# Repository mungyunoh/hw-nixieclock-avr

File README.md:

hw-nixieclock-avr
=============

This project is deprecated and replaced by the arm version.

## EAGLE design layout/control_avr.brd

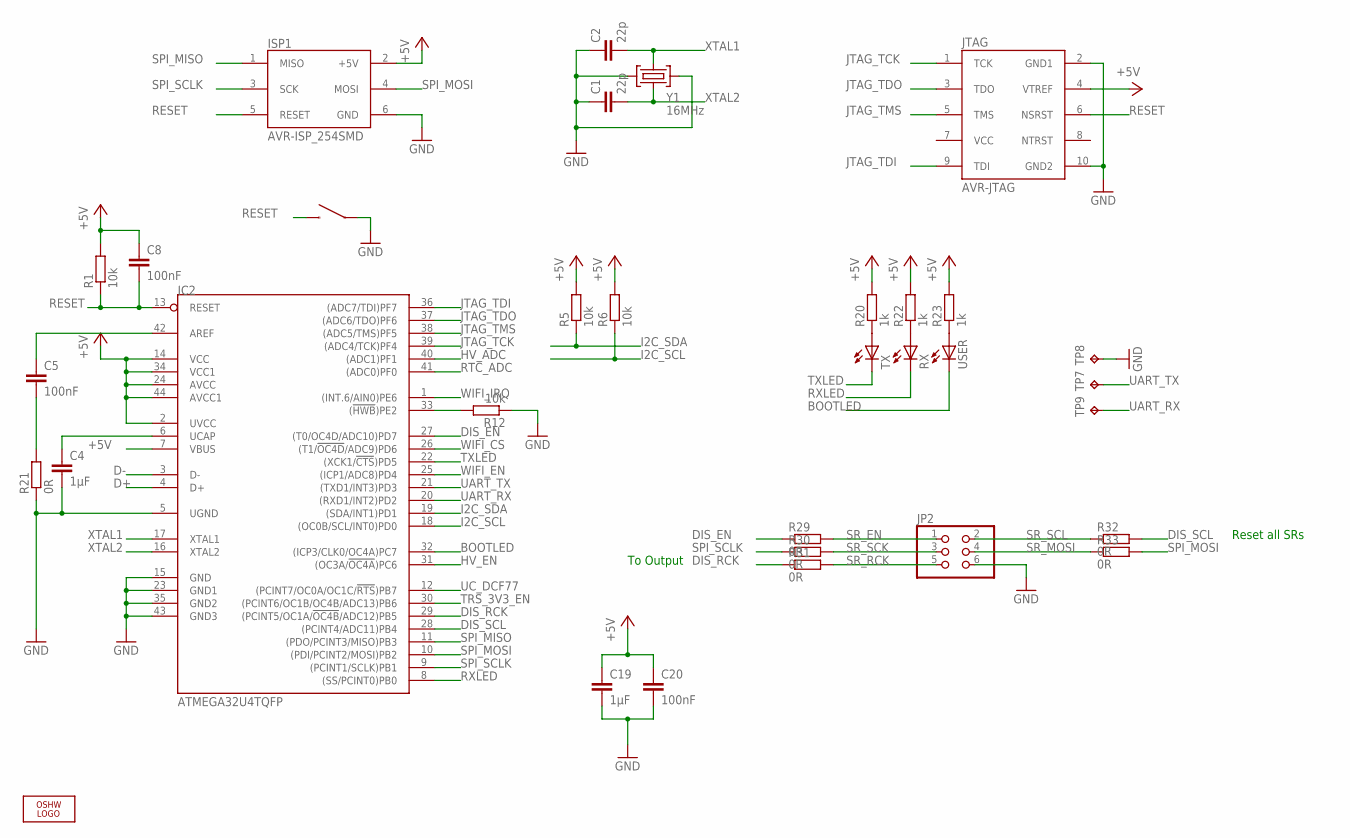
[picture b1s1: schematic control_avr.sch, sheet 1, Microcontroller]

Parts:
C1, C2: 22p; C0603
C4, C19: 1µF; C0603
C5, C8, C20: 100nF; C0603
IC2: ATMEGA32U4TQFP; TQFP44
ISP1: AVR-ISP_254SMD; 2X03SMD
JP2: PINHD-2X3_2.54-SMD-R; 2X03SMD/R
JTAG: AVR-JTAG; 20021121-10010XXLF
LOGO1: OSHW_LOGO_FILLX0200-NT; OSHW_FILLX200_NOTEXT
R1, R5, R6, R12: 10k; R0603
R20, R22, R23: 1k; R0603
R21, R29, R30, R31, R32, R33: 0R; R0603
RESET: TACT-SWITCH-47-35; 47-35
RX: LEDCHIP-LED0603; CHIP-LED0603
TP7, TP9: TPTP10R; TP10R
TP8: TPTP10SQ; TP10SQ
TX: LEDCHIP-LED0603; CHIP-LED0603
USER: LEDCHIP-LED0603; CHIP-LED0603
Y1: 16MHz; X22

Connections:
+5V: C8.1, C19.1, C20.1, IC2.2 (UVCC), IC2.7 (VBUS), IC2.14 (VCC), IC2.24 (AVCC), IC2.34 (VCC1), IC2.44 (AVCC1), ISP1.2 (+5V), JTAG.4 (VTREF), R1.2, R5.2, R6.2, R20.2, R22.2, R23.2; also elsewhere on the board
BOOTLED: IC2.32 ((ICP3/CLK0/OC4A)PC7), USER.C
D+: IC2.4 (D+); also elsewhere on the board
D-: IC2.3 (D-); also elsewhere on the board
DIS_EN: IC2.27 ((T0/OC4D/ADC10)PD7), R29.1
DIS_RCK: IC2.29 ((PCINT5/OC1A/!OC4B!/ADC12)PB5), R31.1
DIS_SCL: IC2.28 ((PCINT4/ADC11)PB4), R32.2
GND: C1.1, C2.1, C4.2, C19.2, C20.2, IC2.5 (UGND), IC2.15 (GND), IC2.23 (GND1), IC2.35 (GND2), IC2.43 (GND3), ISP1.6 (GND), JP2.6, JTAG.2 (GND1), JTAG.10 (GND2), R12.1, R21.1, RESET.C, RESET.D, TP8.TP, Y1.P$1 (GND1), Y1.P$3 (GND2); also elsewhere on the board
HV_ADC: IC2.40 ((ADC1)PF1); also elsewhere on the board
HV_EN: IC2.31 ((OC3A/!OC4A!)PC6); also elsewhere on the board
I2C_SCL: IC2.18 ((OC0B/SCL/INT0)PD0), R6.1; also elsewhere on the board
I2C_SDA: IC2.19 ((SDA/INT1)PD1), R5.1; also elsewhere on the board
JTAG_TCK: IC2.39 ((ADC4/TCK)PF4), JTAG.1 (TCK)
JTAG_TDI: IC2.36 ((ADC7/TDI)PF7), JTAG.9 (TDI)
JTAG_TDO: IC2.37 ((ADC6/TDO)PF6), JTAG.3 (TDO)
JTAG_TMS: IC2.38 ((ADC5/TMS)PF5), JTAG.5 (TMS)
unnamed: R20.1, TX.A
unnamed: IC2.33 ((!HWB!)PE2), R12.2
unnamed: C5.2, R21.2
unnamed: C5.1, IC2.42 (AREF)
unnamed: R22.1, RX.A
unnamed: R23.1, USER.A
RESET: C8.2, IC2.13 (RESET), ISP1.5 (RESET), JTAG.6 (NSRST), R1.1, RESET.A, RESET.B
RTC_ADC: IC2.41 ((ADC0)PF0); also elsewhere on the board
RXLED: IC2.8 ((SS/PCINT0)PB0), RX.C
SPI_MISO: IC2.11 ((PDO/PCINT3/MISO)PB3), ISP1.1 (MISO); also elsewhere on the board
SPI_MOSI: IC2.10 ((PDI/PCINT2/MOSI)PB2), ISP1.4 (MOSI), R33.2; also elsewhere on the board
SPI_SCLK: IC2.9 ((PCINT1/SCLK)PB1), ISP1.3 (SCK), R30.1; also elsewhere on the board
SR_EN: JP2.1, R29.2
SR_MOSI: JP2.4, R33.1
SR_RCK: JP2.5, R31.2
SR_SCK: JP2.3, R30.2
SR_SCL: JP2.2, R32.1
TRS_3V3_EN: IC2.30 ((PCINT6/OC1B/OC4B/ADC13)PB6); also elsewhere on the board
TXLED: IC2.22 ((XCK1/!CTS!)PD5), TX.C
UART_RX: IC2.20 ((RXD1/INT2)PD2), TP9.TP; also elsewhere on the board
UART_TX: IC2.21 ((TXD1/INT3)PD3), TP7.TP
UCAP: C4.1, IC2.6 (UCAP)
UC_DCF77: IC2.12 ((PCINT7/OC0A/OC1C/!RTS!)PB7); also elsewhere on the board
WIFI_CS: IC2.26 ((T1/!OC4D!/ADC9)PD6); also elsewhere on the board
WIFI_EN: IC2.25 ((ICP1/ADC8)PD4); also elsewhere on the board
WIFI_IRQ: IC2.1 ((INT.6/AIN0)PE6); also elsewhere on the board
XTAL1: C2.2, IC2.17 (XTAL1), Y1.CRYSTAL2
XTAL2: C1.2, IC2.16 (XTAL2), Y1.CRYSTAL1

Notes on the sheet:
Reset all SRs
To Output

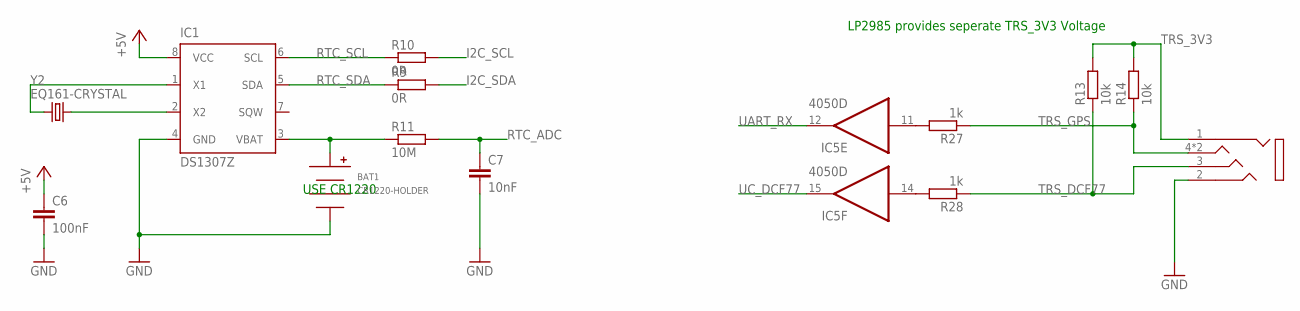
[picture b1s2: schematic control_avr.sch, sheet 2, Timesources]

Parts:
BAT1: CR1220-HOLDER; HARWIN-CR1220
C6: 100nF; C0603
C7: 10nF; C0603
IC1: DS1307Z; SOIC8
IC5: 4050D; SO16
R9, R10: 0R; R0603
R11: 10M; R0603
R13, R14: 10k; R0603
R27, R28: 1k; R0603
U$3: 1503_13; 1503-03
Y2: EQ161-CRYSTAL; EQ161

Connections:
+5V: C6.1, IC1.8 (VCC); also elsewhere on the board
GND: BAT1.NEG, C6.2, C7.2, IC1.4 (GND), U$3.2; also elsewhere on the board
I2C_SCL: R10.2; also elsewhere on the board
I2C_SDA: R9.2; also elsewhere on the board
unnamed: IC1.1 (X1), Y2.P$2 (2)
unnamed: BAT1.POS, IC1.3 (VBAT), R11.1
unnamed: IC1.2 (X2), Y2.P$1 (1)
unnamed: IC5.11 (I), R27.2
unnamed: IC5.14 (I), R28.2
RTC_ADC: C7.1, R11.2; also elsewhere on the board
RTC_SCL: IC1.6 (SCL), R10.1
RTC_SDA: IC1.5 (SDA), R9.1
TRS_3V3: R13.2, R14.2, U$3.1; also elsewhere on the board
TRS_DCF77: R13.1, R28.1, U$3.3
TRS_GPS: R14.1, R27.1, U$3.4, U$3.4-2 (4)
UART_RX: IC5.12 (O); also elsewhere on the board
UC_DCF77: IC5.15 (O); also elsewhere on the board

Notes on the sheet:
LP2985 provides seperate TRS_3V3 Voltage
USE CR1220

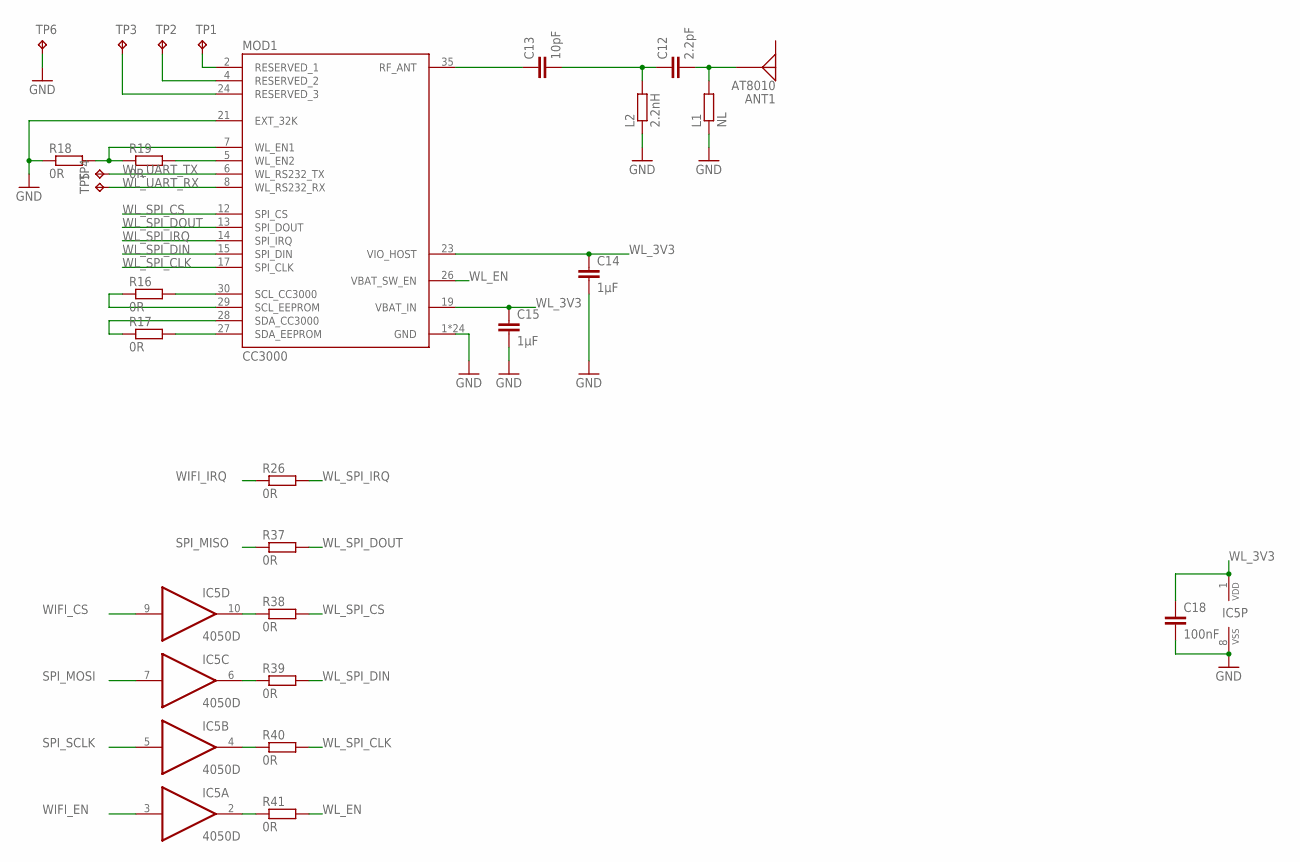
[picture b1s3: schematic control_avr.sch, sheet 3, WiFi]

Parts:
ANT1: AT8010
C12: 2.2pF; C0402
C13: 10pF; C0402
C14, C15: 1µF; C0603
C18: 100nF; C0603
IC5: 4050D; SO16
L1: NL; R0402
L2: 2.2nH; R0402
MOD1: CC3000
R16, R17, R18, R19, R26, R37, R38, R39, R40, R41: 0R; R0603
TP1, TP2, TP3: TPTP06R; TP06R
TP4, TP5: TPTP10R; TP10R
TP6: TPTP10SQ; TP10SQ

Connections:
GND: C14.2, C15.2, C18.2, IC5.8 (VSS), L1.1, L2.1, MOD1.1 (GND), MOD1.9 (GND), MOD1.10 (GND), MOD1.11 (GND), MOD1.16 (GND), MOD1.18 (GND), MOD1.20 (GND), MOD1.21 (EXT_32K), MOD1.22 (GND), MOD1.25 (GND), MOD1.31 (GND), MOD1.32 (GND), MOD1.33 (GND), MOD1.34 (GND), MOD1.36 (GND), MOD1.37 (GND), MOD1.38 (GND), MOD1.39 (GND), MOD1.40 (GND), MOD1.41 (GND), MOD1.42 (GND), MOD1.43 (GND), MOD1.44 (GND), MOD1.45 (GND), MOD1.46 (GND), R18.1, TP6.TP; also elsewhere on the board
unnamed: C13.1, MOD1.35 (RF_ANT)
unnamed: C12.1, C13.2, L2.2
unnamed: ANT1.ANT, C12.2, L1.2
unnamed: MOD1.29 (SCL_EEPROM), R16.1
unnamed: MOD1.30 (SCL_CC3000), R16.2
unnamed: MOD1.27 (SDA_EEPROM), R17.2
unnamed: MOD1.28 (SDA_CC3000), R17.1
unnamed: MOD1.5 (WL_EN2), R19.2
unnamed: MOD1.7 (WL_EN1), R18.2, R19.1
unnamed: MOD1.2 (RESERVED_1), TP1.TP
unnamed: MOD1.4 (RESERVED_2), TP2.TP
unnamed: MOD1.24 (RESERVED_3), TP3.TP
unnamed: IC5.10 (O), R38.1
unnamed: IC5.6 (O), R39.1
unnamed: IC5.4 (O), R40.1
unnamed: IC5.2 (O), R41.1
SPI_MISO: R37.1; also elsewhere on the board
SPI_MOSI: IC5.7 (I); also elsewhere on the board
SPI_SCLK: IC5.5 (I); also elsewhere on the board
WIFI_CS: IC5.9 (I); also elsewhere on the board
WIFI_EN: IC5.3 (I); also elsewhere on the board
WIFI_IRQ: R26.1; also elsewhere on the board
WL_3V3: C14.1, C15.1, C18.1, IC5.1 (VDD), MOD1.19 (VBAT_IN), MOD1.23 (VIO_HOST); also elsewhere on the board
WL_EN: MOD1.26 (VBAT_SW_EN), R41.2
WL_SPI_CLK: MOD1.17 (SPI_CLK), R40.2
WL_SPI_CS: MOD1.12 (SPI_CS), R38.2
WL_SPI_DIN: MOD1.15 (SPI_DIN), R39.2
WL_SPI_DOUT: MOD1.13 (SPI_DOUT), R37.2
WL_SPI_IRQ: MOD1.14 (SPI_IRQ), R26.2
WL_UART_RX: MOD1.8 (WL_RS232_RX), TP5.TP
WL_UART_TX: MOD1.6 (WL_RS232_TX), TP4.TP

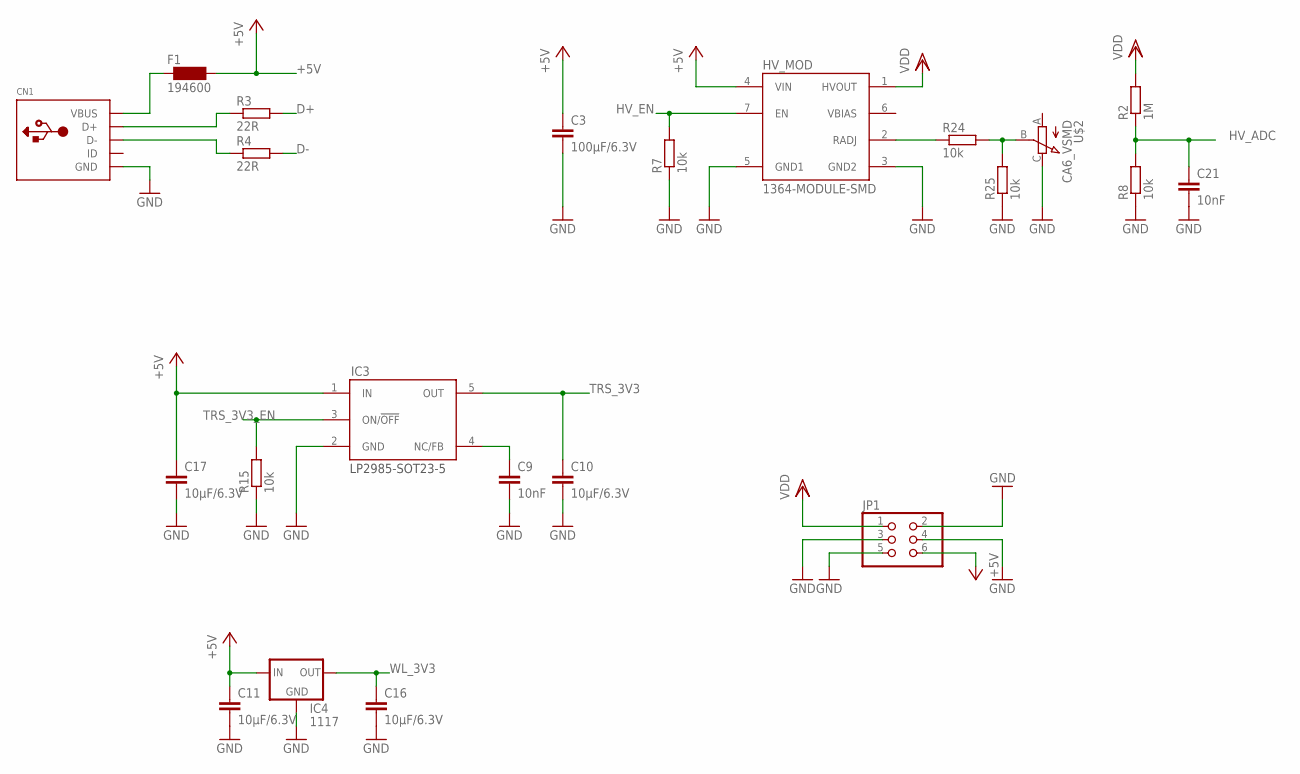
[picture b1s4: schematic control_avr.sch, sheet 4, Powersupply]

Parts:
C3: 100µF/6.3V; C1210
C9, C21: 10nF; C0603
C10, C11, C16, C17: 10µF/6.3V; C0603
CN1: USBMINIB; USB-MINIB
F1: 194600; 1812
HV_MOD: 1364-MODULE-SMD; 1364-SMD
IC3: LP2985-SOT23-5; SOT23-5
IC4: 1117; SOT223
JP1: PINHD-2X3_2.54-SMD-R; 2X03SMD/R
R2: 1M; R1206
R3, R4: 22R; R0603
R7, R8, R15, R24, R25: 10k; R0603
U$2: CA6_VSMD; CA6-VSMD

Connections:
+5V: C3.1, C11.1, C17.1, F1.P$2, HV_MOD.4 (VIN), IC3.1 (IN), IC4.3 (IN), JP1.6; also elsewhere on the board
D+: R3.2; also elsewhere on the board
D-: R4.2; also elsewhere on the board
GND: C3.2, C9.2, C10.2, C11.2, C16.2, C17.2, C21.2, CN1.GND, HV_MOD.3 (GND2), HV_MOD.5 (GND1), IC3.2 (GND), IC4.1 (GND), JP1.2, JP1.3, JP1.4, JP1.5, R7.1, R8.1, R15.1, R25.1, U$2.C (E); also elsewhere on the board
HV_ADC: C21.1, R2.1, R8.2; also elsewhere on the board
HV_EN: HV_MOD.7 (EN), R7.2; also elsewhere on the board
unnamed: CN1.D-, R4.1
unnamed: CN1.D+, R3.1
unnamed: CN1.VBUS, F1.P$1
unnamed: HV_MOD.2 (RADJ), R24.1
unnamed: R24.2, R25.2, U$2.B (S)
unnamed: C9.1, IC3.4 (NC/FB)
TRS_3V3: C10.1, IC3.5 (OUT); also elsewhere on the board
TRS_3V3_EN: IC3.3 (ON/!OFF), R15.2; also elsewhere on the board
VDD: HV_MOD.1 (HVOUT), JP1.1, R2.2
WL_3V3: C16.1, IC4.2 (OUT), IC4.4 (OUT); also elsewhere on the board

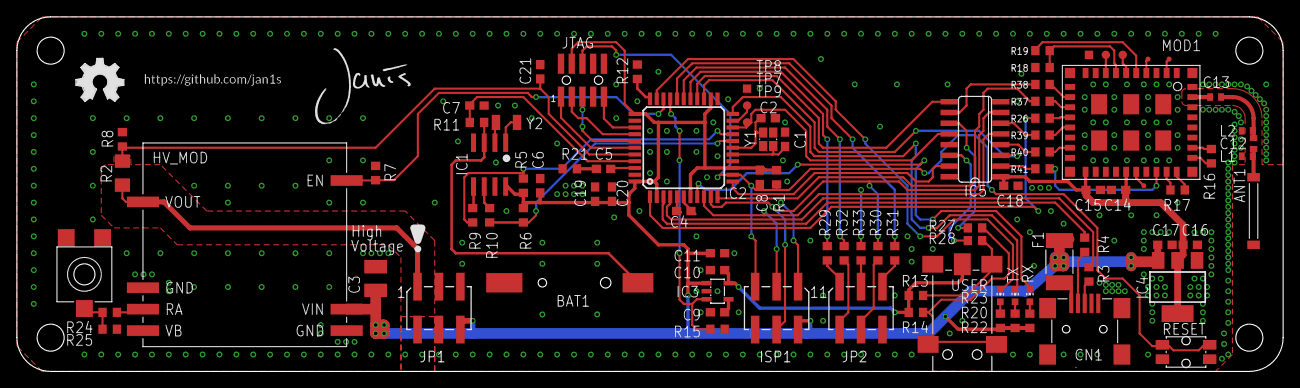
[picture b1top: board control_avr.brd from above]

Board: 2 copper layers, 150.0 x 42.0 mm, 96 parts (0 on the bottom side), 86 nets.

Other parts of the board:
U$1: JANIS_10MM
U$5: GITHUB/JAN1S
